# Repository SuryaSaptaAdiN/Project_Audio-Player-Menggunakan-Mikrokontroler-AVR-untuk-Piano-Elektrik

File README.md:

# Audio Player Menggunakan Mikrokontroler AVR untuk Piano Elektrik 
## Workshop Mikrokonroler // D3 Teknik Elektronika A // <a href="https://www.pens.ac.id/" target="_blank">Politeknik Elektronika Negeri Surabaya</a>
DOSEN PENGAMPU : Akhmad Hendriawan ST, MT  
NIP. 197501272002121003

https://github.com/SuryaSaptaAdiN/Project_Audio-Player-Menggunakan-Mikrokontroler-AVR-untuk-Piano-Elektrik/assets/168740916/dbf298af-808a-47be-9ff9-27a4f887b5b3

Video Ads dari Piano Elektrik dapat dilihat pada: <a href="https://www.youtube.com/watch?v=zn1vYoaUdRE" target="_blank">Video Ads</a>

Video Presentasi dari Piano Elektrik dapat dilihat pada: <a href="https://youtu.be/qKnIm3eNd0Y" target="_blank">Video presentation Project</a>

DIBUAT OLEH:
| No.  | Nama  | NRP  | Status  |
| :------------: | :------------: | :------------: | :------------: |
| 1  | Surya Sapta Adi Nugraha  | 2122500014  | Project Manager  |
| 2  | Abimanyu Fajar Ramadhan  | 2122500008  | Designer Hardware  |
| 3  |  Abdullah Hanafi Salim  | 2122500010  |  Programmer |
| 4  |  Gusma Kemal Pasha |  2122500011 | PCB Maker |
| 5  |  Salsabillah Whita Rosa | 2122500022  |  Audio Editor |
| 6  | Hambali Ahmad  |  2122500027 | Dokumenter  |

## Daftar Isi
- [Deskripsi](#Deskripsi)
- [Fitur](#Fitur)
- [Alat dan Bahan](#Alat-dan-Bahan)
  - [Daftar Alat Software](#Daftar-Alat-Software)
  - [Daftar Alat dan Bahan Hardware](#Daftar-Alat-dan-Bahan-Hardware)
- [Konsep Kerja](#Konsep-Kerja)
  - [Blok Diagram](#Blok-Diagram)
  - [Cara Kerja](#Cara-Kerja)
- [Detail Proyek](#Detail-Proyek)
  - [PCB](#PCB)
    - [Desain Skematik Shield Arduino](#Desain-Skematik-Shield-Arduino)
    - [Desain Shield PCB](#Desain-Shield-PCB)
    - [Desain Sistem Proyek](#Desain-Sistem-Proyek)
    - [Video Desain PCB](#Video-Desain-PCB)
    - [Hasil Gambar PCB](#Hasil-Gambar-PCB)
  - [3D Kemasan Proyek](#3D-Kemasan-Proyek)
    - [Desain 3D Case Arduino](#Desain-3D-Case-Arduino)
    - [Video Pembuatan Desain 3D](#Video-Pembuatan-Desain-3D)
    - [Foto 3D](#Foto-3D)
  - [Program](#Program)
    - [Convert Audio](#Convert-Audio)
    - [Video Convert Audio](#Video-Convert-Audio)
    - [Simulasi Program](#Simulasi-Program)
    - [Video Simulasi](#Video-Simulasi)
    - [Realisasi Program](#Realisasi-Program)
    - [Realisasi EEPROM](#Realisasi-EEPROM)
- [Dokumentasi Proyek dan Team](#Dokumentasi-Proyek-dan-Team)
  
## Deskripsi
Proyek digital audio player adalah sebuah sistem yang memungkinkan pembangkitan dan pemutaran sinyal audio melalui mikrokontroler AVR. Dalam Proyek ini membuat alat musik piano elektrik yang mampu mengisi waktu luang dengan memainkan alat musik dan memudahkan pengguna untuk membawa piano elektrik ini. Output audio yang dibangkitkan dikeluarkan ke speaker aktif untuk memastikan kualitas suara yang baik.

## Fitur
- Pembangkitan sinyal audio melalui mikrokontroler AVR.
- Tombol push button untuk memainkan nada tertentu.
- Output audio dikeluarkan ke speaker aktif.

## Alat dan Bahan
### Daftar Alat Software
1. Visual Studio Code
2. Github
3. Git
4. Autodesk Fusion 360
5. Eagle
6. Wokwi
### Daftar Alat dan Bahan Hardware
| No.  | Nama Barang  | Jumlah  |
| :------------: | :------------: | :------------: |
| 1  | Arduino ATmega 2560  | 1x  |
| 2  | Push Button  | 8x  |
| 3  |  Switch  | 1x  |
| 4  |  Switch 3 pin |  1x |
| 5  |  Speaker | 1x  |
| 6  | Baterai 9V  |  1x |
| 7  | Resistor 220ohm |  1x |

## Konsep Kerja
### Blok Diagram

### Cara Kerja
Proyek Audio Player untuk Piano Elektrik ini beroperasi dengan menggunakan mikrokontroler AVR sebagai pusat pengendalian. Sumber daya untuk proyek ini disediakan oleh baterai 9V, yang alirannya dapat diatur melalui saklar ON/OFF. Mikrokontroler ini terhubung ke berbagai komponen lainnya. Ada delapan push button, setiap tombol ini berfungsi untuk memainkan nada yang berbeda pada piano elektrik. Terdapat switch tiga pin sebagai pergantian mode nada piano elektrik. Pada mode I (kiri) mengeluarkan nada rendah, pada mode 0 (tengah) mengeluarkan nada normal, dan II (kanan) akan mengeluarkan nada tinggi. Selain itu, ada port input audio yang diberi label “JACK IN” yang akan menghubungkan mikrokontroler dengan speaker eksternal. Speaker ekternal digunakan untuk menghasilkan suara piano. Dengan demikian, proyek ini menciptakan sistem pemutar audio ketika ditekan yang dapat memainkan seperti suara piano.

## Detail Proyek
### PCB
#### Desain Skematik Shield Arduino

Detail desain skematik dapat dilihat pada: <a href="https://github.com/SuryaSaptaAdiN/Project_Audio-Player-Menggunakan-Mikrokontroler-AVR-untuk-Piano-Elektrik/tree/main/PCB" target="_blank">Design Schematic</a>

#### Desain Shield PCB

Detail desain shield PCB dapat dilihat pada: <a href="https://github.com/SuryaSaptaAdiN/Project_Audio-Player-Menggunakan-Mikrokontroler-AVR-untuk-Piano-Elektrik/tree/main/PCB" target="_blank">Design Board & Manufacturing</a>

#### Desain Sistem Proyek

Detail desain skematik dapat dilihat pada: <a href="https://github.com/SuryaSaptaAdiN/Project_Audio-Player-Menggunakan-Mikrokontroler-AVR-untuk-Piano-Elektrik/tree/main/Simulation" target="_blank">Design Sistem</a>

#### Video Desain PCB
Tutorial desain  PCB dapat dilihat pada link berikut:
<a href="https://drive.google.com/file/d/1Dn3zpLJODagx13IVd2wvJaMp7lEnFp5E/view?usp=sharing">Video Tutorial Design PCB by Gusma</a>

#### Hasil Gambar PCB

Detail hasil desain PCB dapat dilihat pada: <a href="https://github.com/SuryaSaptaAdiN/Project_Audio-Player-Menggunakan-Mikrokontroler-AVR-untuk-Piano-Elektrik/tree/main/PCB" target="_blank">Pict PCB</a>

### 3D Kemasan Proyek
#### Desain 3D Case Arduino

Detail desain untuk case arduino dapat dilihat pada: <a href="https://github.com/SuryaSaptaAdiN/Project_Audio-Player-Menggunakan-Mikrokontroler-AVR-untuk-Piano-Elektrik/tree/main/3D%20Package" target="_blank">Design Package</a> atau <a href="https://www.thingiverse.com/thing:6646377" target="_blank">Thingiverse</a>

Keterangan Ukuran:
- Panjang bagian bawah 172mm
- Lebar bagian bawah 96mm
- Tinggi bagian bawah 17mm
- Panjang bagian atas 168mm
- Lebar bagian atas 62mm
- Tinggi bagian atas 8mm
- lubang jack 10mm

#### Video Pembuatan Desain 3D

Tutorial pembuatan desain 3D untuk pengemasan alat proyek dapat dilihat pada link berikut:
<a href="https://www.youtube.com/watch?v=R6Fa050dKPA" target="_blank">Video Tutorial Design 3D by Abimanyu</a>

#### Foto 3D

Detail foto untuk kemasan dapat dilihat pada: <a href="https://github.com/SuryaSaptaAdiN/Project_Audio-Player-Menggunakan-Mikrokontroler-AVR-untuk-Piano-Elektrik/tree/main/3D%20Package" target="_blank">Pict Package</a>

### Program
#### Convert Audio
Data dari semua tuts piano yang telah dikonversi dapat dilihat pada: <a href="https://github.com/SuryaSaptaAdiN/Project_Audio-Player-Menggunakan-Mikrokontroler-AVR-untuk-Piano-Elektrik/tree/main/Tuts%20Piano" target="_blank">All Audio Piano</a>.

#### Video Convert Audio
Tutorial mengkonversi audio dapat dilihat pada link berikut:
<a href="https://drive.google.com/file/d/1lOgqFtMnbho2i-TdwihDMigcp6qOo6Ut/view" target="_blank">Video Tutorial Convert Audio by Salsabillah</a>

#### Simulasi Program
Simulasi dapat dilihat pada: <a href="https://wokwi.com/projects/398312099364933633" target="_blank">Wokwi Simulation</a>.

Detail dari simulasi dapat dilihat pada: <a href="https://github.com/SuryaSaptaAdiN/Project_Audio-Player-Menggunakan-Mikrokontroler-AVR-untuk-Piano-Elektrik/tree/main/Simulation" target="_blank">Simulation Github</a>.
#### Video Simulasi
Simulasi dari program melalui software wokwi dapat dilihat pada link berikut:
<a href="https://youtu.be/XzKsaTkORDI?si=tM6pIqVIvMEymQc2" target="_blank">Video Simulation Wokwi by Surya & Hanafi</a>

Simulasi alat piano dapat dilihat pada video berikut:

https://github.com/SuryaSaptaAdiN/Project_Audio-Player-Menggunakan-Mikrokontroler-AVR-untuk-Piano-Elektrik/assets/168740916/93c877ef-d919-4c5d-9aa7-36d04b013b71

#### Realisasi Program
Bentuk realisasi final program dapat dilihat pada: <a href="https://github.com/SuryaSaptaAdiN/Project_Audio-Player-Menggunakan-Mikrokontroler-AVR-untuk-Piano-Elektrik/blob/main/Program/Audio%20Player/src/main.cpp" target="_blank">Main Program</a>

Penjelasan detail dari program dapat dilihat pada link berikut:
<a href="https://drive.google.com/file/d/1Dn3zpLJODagx13IVd2wvJaMp7lEnFp5E/view?usp=sharing" target="_blank">Video Program by Hanafi</a>

#### Realisasi EEPROM
Bentuk realisasi EEPROM dapat dilihat pada: <a href="https://github.com/SuryaSaptaAdiN/Project_Audio-Player-Menggunakan-Mikrokontroler-AVR-untuk-Piano-Elektrik/blob/main/Program/Audio%20Player/src/pitches.h" target="_blank">EEPROM Program</a>

## Dokumentasi Proyek dan Team
https://github.com/SuryaSaptaAdiN/Project_Audio-Player-Menggunakan-Mikrokontroler-AVR-untuk-Piano-Elektrik/assets/168740916/ee1586a2-95dd-4360-ae75-e725f54b5b29

https://github.com/SuryaSaptaAdiN/Project_Audio-Player-Menggunakan-Mikrokontroler-AVR-untuk-Piano-Elektrik/assets/168740916/f328bb08-1285-4355-9b0a-1f4d35c735a2

Detail selengkapnya mengenai dokumentasi yang berhubungan dengan proyek atau seputar team dapat dilihat pada: <a href="https://github.com/SuryaSaptaAdiN/Project_Audio-Player-Menggunakan-Mikrokontroler-AVR-untuk-Piano-Elektrik/tree/main/About%20Project" target="_blank">About Project</a>

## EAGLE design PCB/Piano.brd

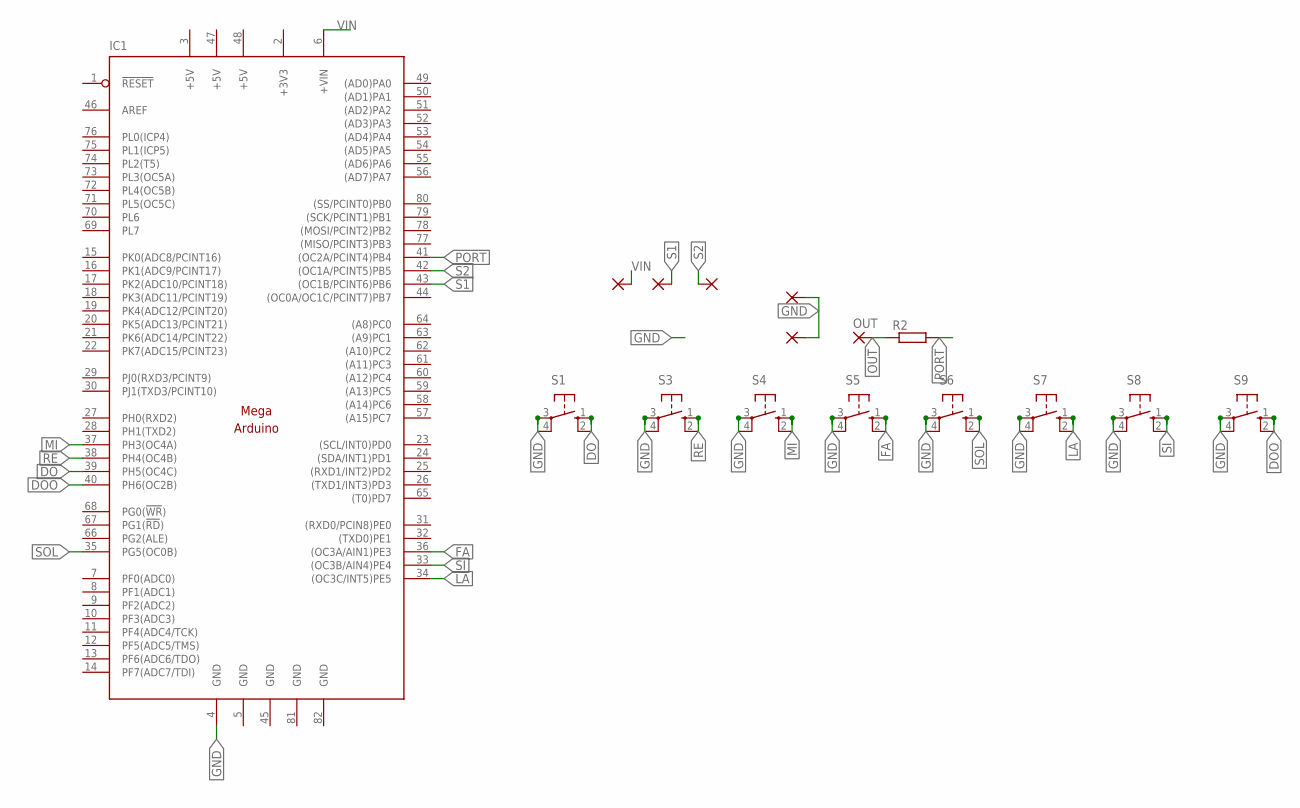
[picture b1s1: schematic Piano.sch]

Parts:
IC1: MEGAARDUINO_12; MEGA_ARDUINO_2
OUT: 2,54/1,1
PAD1, PAD2, PAD3, PAD4, PAD5: 2,54/1,1
R2: R-EU_0411/12; 0411/12
S1, S3, S4, S5, S6, S7, S8, S9: 40-XX; B3F-40XX

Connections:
+3V3: IC1.2 (+3V3)
+5V: IC1.3 (+5V), IC1.47 (+5V), IC1.48 (+5V)
DO: IC1.39 (PH5(OC4C)), S1.1 (S), S1.2 (S1)
DOO: IC1.40 (PH6(OC2B)), S9.1 (S), S9.2 (S1)
FA: IC1.36 ((OC3A/AIN1)PE3), S5.1 (S), S5.2 (S1)
GND: IC1.4 (GND), IC1.5 (GND), IC1.45 (GND), IC1.81 (GND), IC1.82 (GND), PAD1.1, PAD2.1, S1.3, S1.4 (P1), S3.3, S3.4 (P1), S4.3, S4.4 (P1), S5.3, S5.4 (P1), S6.3, S6.4 (P1), S7.3, S7.4 (P1), S8.3, S8.4 (P1), S9.3, S9.4 (P1)
LA: IC1.34 ((OC3C/INT5)PE5), S7.1 (S), S7.2 (S1)
MI: IC1.37 (PH3(OC4A)), S4.1 (S), S4.2 (S1)
OUT: OUT.1, R2.1
PORT: IC1.41 ((OC2A/PCINT4)PB4), R2.2
RE: IC1.38 (PH4(OC4B)), S3.1 (S), S3.2 (S1)
S1: IC1.43 ((OC1B/PCINT6)PB6), PAD3.1
S2: IC1.42 ((OC1A/PCINT5)PB5), PAD4.1
SI: IC1.33 ((OC3B/AIN4)PE4), S8.1 (S), S8.2 (S1)
SOL: IC1.35 (PG5(OC0B)), S6.1 (S), S6.2 (S1)
VIN: IC1.6 (+VIN), PAD5.1

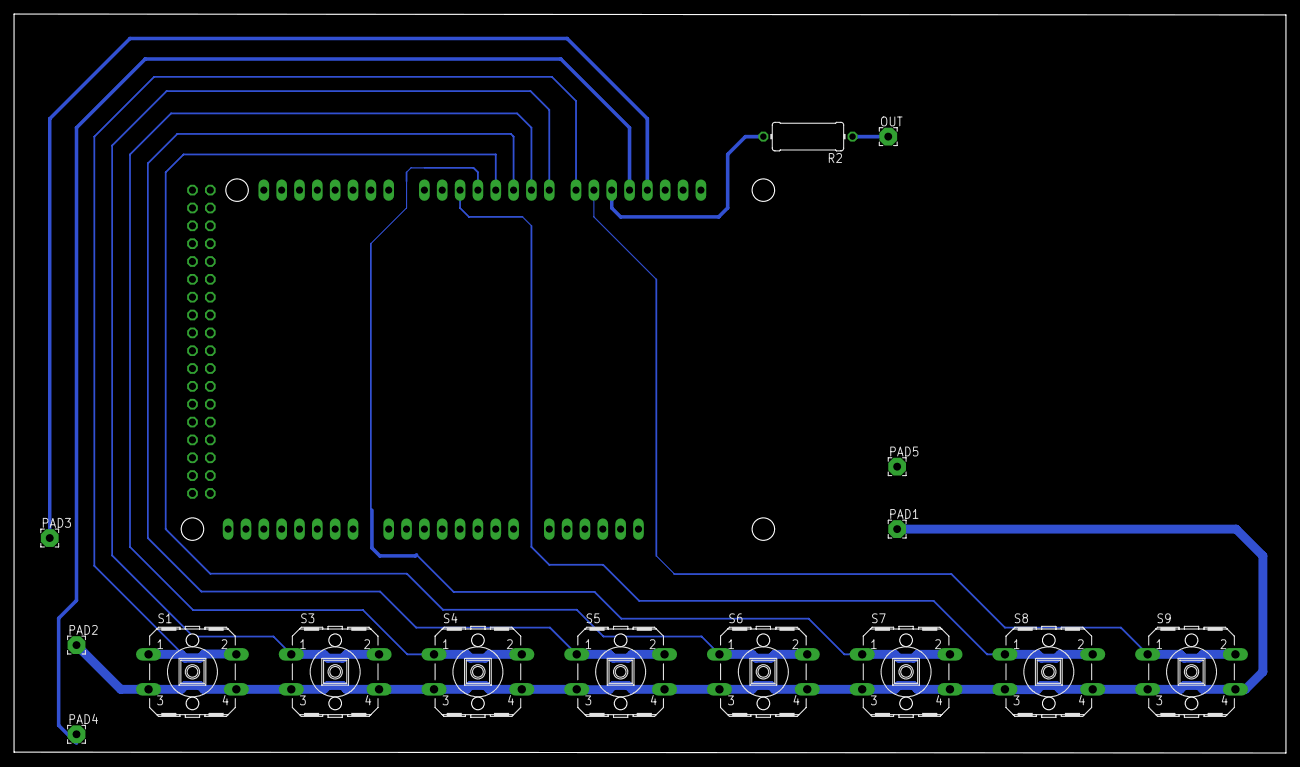
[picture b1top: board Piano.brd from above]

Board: 2 copper layers, 181.1 x 105.2 mm, 16 parts (1 on the bottom side), 15 nets.

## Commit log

2024-05-05 Task Project
2024-05-05 Add README
2024-05-13 README.md
2024-05-19 Coding Program
2024-05-19 add audio
2024-05-19 add simulation
2024-05-20 datasheet
2024-05-20 add for simulation
2024-05-20 poster
2024-05-24 others
2024-05-26 design package
2024-05-26 video simulation
2024-05-27 design pcb
2024-05-28 pict package
2024-06-01 dokumentasi
2024-06-02 all simulation
2024-06-02 add program
